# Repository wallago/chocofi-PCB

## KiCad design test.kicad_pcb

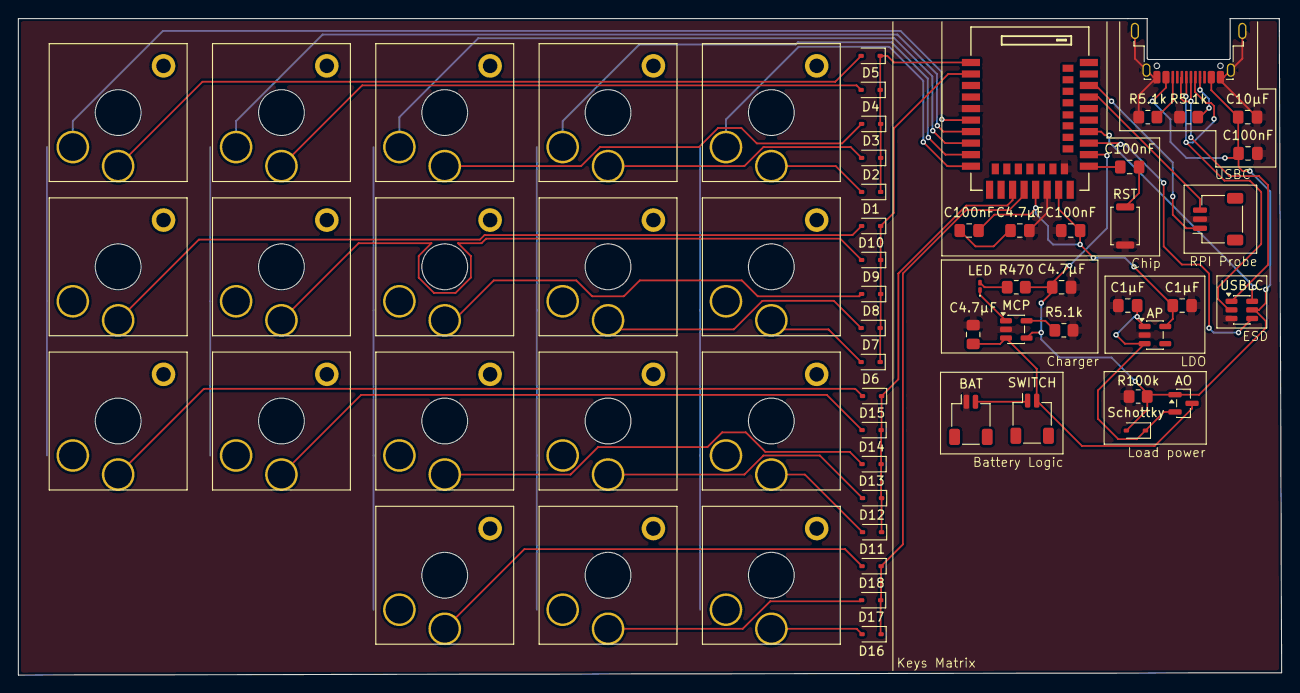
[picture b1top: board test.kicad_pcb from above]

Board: 2 copper layers, 139.2 x 72.4 mm, 63 parts (0 on the bottom side), 47 nets.

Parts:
AO: AO3401A; SOT-23
AP: AP2112K-3.3; SOT-23-5
BAT: Conn_01x02_Pin (battery); JST_SH_SM02B-SRSS-TB_1x02-1MP_P1.00mm_Horizontal
C1µF, C1µF#2: C (1µF); C_0805_2012Metric_Pad1.18x1.45mm_HandSolder
C4.7µF, C4.7µF#2, C4.7µF#3: C (4.7µF); C_0805_2012Metric_Pad1.18x1.45mm_HandSolder
C10µF: C (10µF); C_0805_2012Metric_Pad1.18x1.45mm_HandSolder
C100nF, C100nF#2, C100nF#3, C100nF#4: C (100nF); C_0805_2012Metric_Pad1.18x1.45mm_HandSolder
D1, D2, D3, D4, D5, D6, D7, D8, D9, D10, D11, D12, D13, D14, D15, D16, D17, D18: 1N4148WS; D_SOD-323
J1: USB_C_Receptacle_USB2.0_16P; USB_C_Receptacle_Amphenol_12401948E412A
J4: Conn_01x03_Pin; JST_SH_SM03B-SRSS-TB_1x03-1MP_P1.00mm_Horizontal
LED: LED; LED_0201_0603Metric_Pad0.64x0.40mm_HandSolder
MCP: MCP73831-2-OT; SOT-23-5
R5.1k, R5.1k#3: R (5.1k); R_0805_2012Metric_Pad1.20x1.40mm_HandSolder
R5.1k#2: R (5k); R_0805_2012Metric_Pad1.20x1.40mm_HandSolder
R100k: R (100k); R_0805_2012Metric_Pad1.20x1.40mm_HandSolder
R470: R (470); R_0805_2012Metric_Pad1.20x1.40mm_HandSolder
RST: SW_Push; SW_Push_SPST_NO_Alps_SKRK
SW1, SW2, SW3, SW4, SW5, SW6, SW7, SW8, SW9, SW10, SW11, SW12, SW13, SW14, SW15, SW16, SW17, SW18: SW_Push; SW_Hotswap_Kailh_Choc_V2_Plated
SWITCH: Conn_01x02_Pin (switch); JST_SH_SM02B-SRSS-TB_1x02-1MP_P1.00mm_Horizontal
Schottky: D_Schottky; D_SOD-323
U1: E73-2G4M08S1C
USBLC: USBLC6-2SC6; SOT-23-6

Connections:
3v3: AP.5 (VOUT), C1µF#2.1, C100nF#2.2, C100nF#4.1, U1.19 (VDD), U1.23 (VDDH)
BAT: AO.3 (D), C4.7µF#2.1, MCP.3 (V_{BAT}), SWITCH.2
D+ (post-ESD): U1.31 (D+), USBLC.6 (I/O1)
D+ (pre-ESD): J1.A6 (D+), J1.B6 (D+), USBLC.1 (I/O1)
D- (post-ESD): U1.29 (D-), USBLC.4 (I/O2)
D- (pre-ESD): J1.A7 (D-), J1.B7 (D-), USBLC.2 (GND)
GND: AP.2 (GND), BAT.1, C1µF.1, C1µF#2.2, C4.7µF.2, C4.7µF#2.2, C4.7µF#3.1, C10µF.1, C100nF.1, C100nF#2.1, J1.A1 (GND), J1.A12 (GND), J1.B1 (GND), J1.B12 (GND), J1.SH (SHIELD), J4.2, MCP.2 (V_{SS}), R5.1k.1, R5.1k#2.1, R5.1k#3.1, R100k.1, RST.1, U1.5 (GND), U1.21 (GND), U1.24 (GND), USBLC.3 (I/O2)
unnamed: C100nF#3.1, RST.2
unnamed: C4.7µF.1, C100nF#4.2
unnamed: D1.2 (A), SW1.1
unnamed: D2.2 (A), SW2.1
unnamed: D3.2 (A), SW3.1
unnamed: D4.2 (A), SW4.1
unnamed: D5.2 (A), SW5.1
unnamed: D6.2 (A), SW6.1
unnamed: D7.2 (A), SW7.1
unnamed: D8.2 (A), SW8.1
unnamed: D9.2 (A), SW9.1
unnamed: D10.2 (A), SW10.1
unnamed: D11.2 (A), SW11.1
unnamed: D12.2 (A), SW12.1
unnamed: D13.2 (A), SW13.1
unnamed: D14.2 (A), SW14.1
unnamed: D15.2 (A), SW15.1
unnamed: D16.2 (A), SW16.1
unnamed: D17.2 (A), SW17.1
unnamed: D18.2 (A), SW18.1
unnamed: LED.2 (A), R470.1
unnamed: LED.1 (K), MCP.1 (STAT)
unnamed: J1.A5 (CC1), R5.1k.2
unnamed: J1.B5 (CC2), R5.1k#3.2
unnamed: BAT.2, SWITCH.1
unnamed: C100nF#3.2, U1.26 (P0.18/RESET)
unnamed: MCP.5 (PROG), R5.1k#2.2
SWDCLK: J4.1, U1.39 (SWDCLK)
SWDIO: J4.3, U1.37 (SWDIO)
VBUS: AO.1 (G), C4.7µF#3.2, C10µF.2, C100nF.2, J1.A4 (VBUS), J1.A9 (VBUS), J1.B4 (VBUS), J1.B9 (VBUS), MCP.4 (V_{DD}), R100k.2, R470.2, Schottky.2 (A), U1.27 (VBUS), USBLC.5 (VBUS)
VSYS: AO.2 (S), AP.1 (VIN), AP.3 (EN), C1µF.2, Schottky.1 (K)
col_1: SW1.2, SW6.2, SW11.2, SW16.2, U1.10 (P0.30/AIN6*)
col_2: SW2.2, SW7.2, SW12.2, SW17.2, U1.9 (P0.31/AIN7*)
col_3: SW3.2, SW8.2, SW13.2, SW18.2, U1.8 (P0.29/AIN5*)
col_4: SW4.2, SW9.2, SW14.2, U1.7 (P0.02/AIN0*)
col_5: SW5.2, SW10.2, SW15.2, U1.6 (P1.13*)
row_1: D1.1 (K), D2.1 (K), D3.1 (K), D4.1 (K), D5.1 (K), U1.1 (P1.11*)
row_2: D6.1 (K), D7.1 (K), D8.1 (K), D9.1 (K), D10.1 (K), U1.2 (P1.10*)
row_3: D11.1 (K), D12.1 (K), D13.1 (K), D14.1 (K), D15.1 (K), U1.15 (P0.05/AIN3)
row_4: D16.1 (K), D17.1 (K), D18.1 (K), U1.17 (P1.09)

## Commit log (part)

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2026-05-12 feat: init
2026-05-14 feat: add flake
2026-05-15 feat: init pcb
2026-05-15 feat(pcb): upgrade it
2026-06-03 feat: update it by adding load power path
